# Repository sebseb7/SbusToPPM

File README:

This small Converter converts Futaba SBus Signal (inverted serial 100000 baud) to PPM (Pulse Position Modulation) or Spektrum Serial (serial 115200 baud)

I also sell them for 10 Euro (complete) or 1 Euro (pcb only)

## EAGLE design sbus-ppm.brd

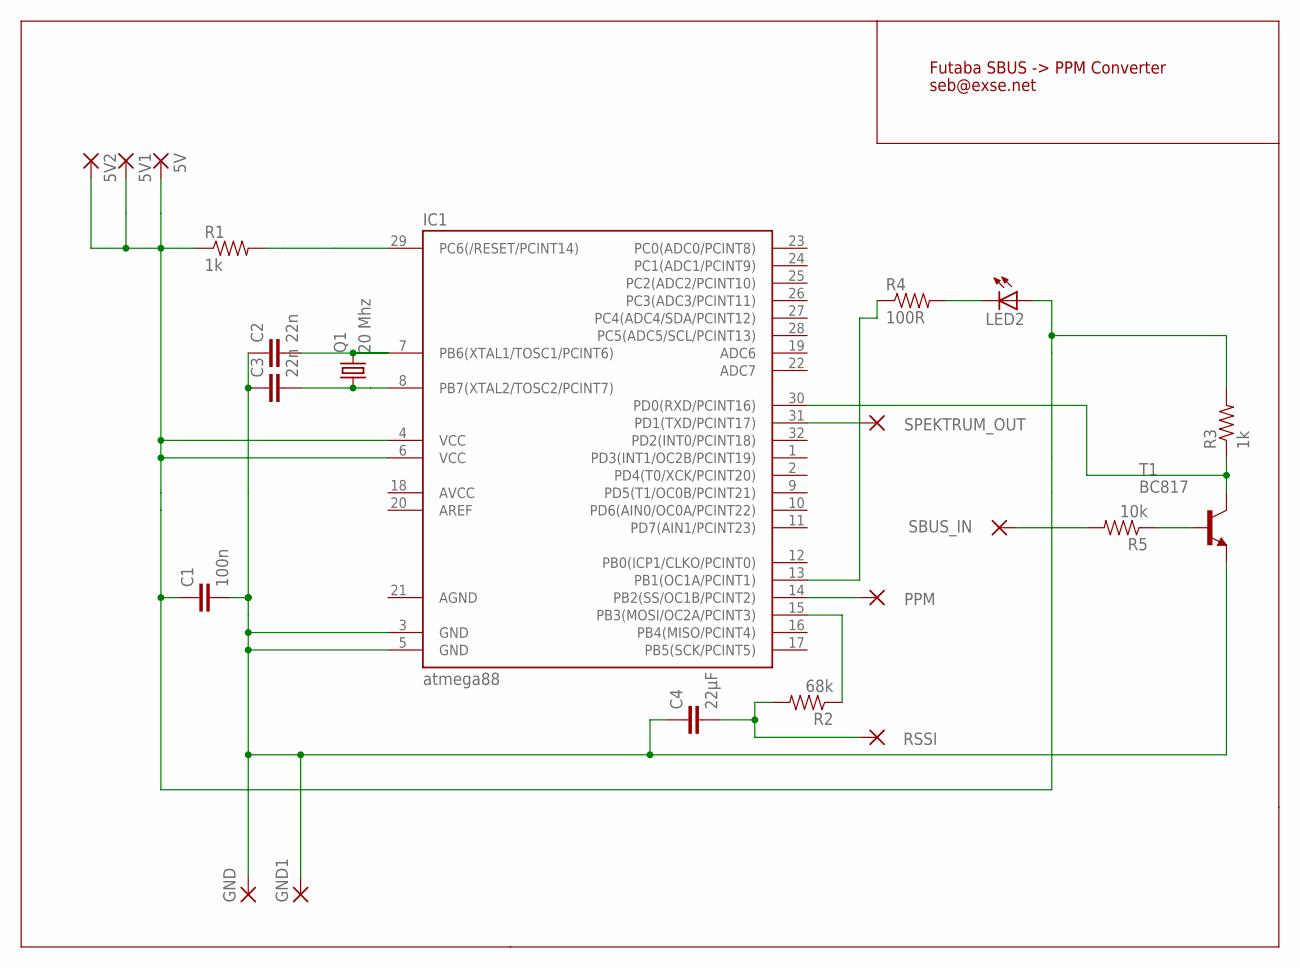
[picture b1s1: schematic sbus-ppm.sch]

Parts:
5V, 5V1, 5V2: SMD2; SMD1,27-2,54
C1: 100n; 0805
C2, C3: 22n; 0805
C4: 22µF; 0805
GND, GND1: SMD2; SMD1,27-2,54
IC1: atmega88; TQFP32-08
LED2: LEDCHIPLED_0805; CHIPLED_0805
PPM: SMD2; SMD1,27-2,54
Q1: 20 Mhz; X22
R1, R3: 1k; 0805
R2: 68k; 0805
R4: 100R; 0805
R5: 10k; 0805
RSSI: SMD2; SMD1,27-2,54
SBUS_IN: SMD2; SMD1,27-2,54
SPEKTRUM_OUT: SMD2; SMD1,27-2,54
T1: BC817; SOT23

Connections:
+5V: 5V.1, 5V1.1, 5V2.1, C1.1, IC1.4 (VCC), IC1.6 (VCC), LED2.A, R1.1, R3.2
AGND: IC1.21 (AGND)
GND: C1.2, C2.1, C3.1, C4.1, GND.1, GND1.1, IC1.3 (GND), IC1.5 (GND), T1.2 (E)
unnamed: IC1.15 (PB3(MOSI/OC2A/PCINT3)), R2.1
unnamed: IC1.14 (PB2(SS/OC1B/PCINT2)), PPM.1
unnamed: R5.2, SBUS_IN.1
unnamed: C4.2, R2.2, RSSI.1
unnamed: IC1.29 (PC6(/RESET/PCINT14)), R1.2
unnamed: C3.2, IC1.8 (PB7(XTAL2/TOSC2/PCINT7)), Q1.1
unnamed: C2.2, IC1.7 (PB6(XTAL1/TOSC1/PCINT6)), Q1.3 (2)
unnamed: R5.1, T1.1 (B)
unnamed: IC1.31 (PD1(TXD/PCINT17)), SPEKTRUM_OUT.1
unnamed: LED2.C, R4.2
unnamed: IC1.13 (PB1(OC1A/PCINT1)), R4.1
unnamed: IC1.30 (PD0(RXD/PCINT16)), R3.1, T1.3 (C)

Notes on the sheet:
Futaba SBUS -> PPM Converter
seb@exse.net

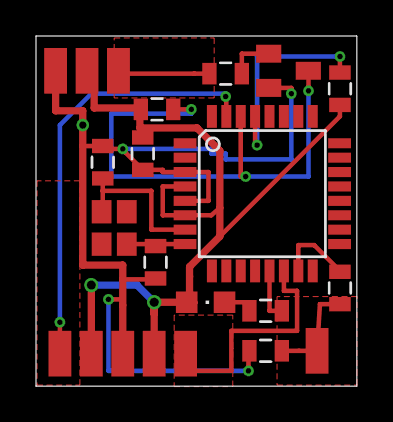
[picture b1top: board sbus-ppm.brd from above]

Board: 2 copper layers, 17.8 x 19.5 mm, 22 parts (0 on the bottom side), 14 nets.

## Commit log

2011-06-28 initial
2011-06-28 cleanup / gitignore
2011-06-28 cleanup
2011-07-01 removed check that could lead to problems
2011-07-01 added picture
2011-07-01 typo
2011-07-14 Edited README.mkd via GitHub
2012-02-27 whitespace cleanup
2012-02-27 new small Makefile
2012-07-11 readded as v6
2014-02-07 Update S-BUS -> PPM conversion
    Actual pulse widths and S-BUS values were read from a Futaba
    receiver, and a linear regression was used to determine a best fit for
    the measurements.
    The code and data used for the derivation can be found at
    https://gist.github.com/prattmic/8857047
    Basically, the S-BUS and raw PWM outputs were read from the Futaba
2014-02-07 Remove 'sei' in interrupt
    By definition, interrupts must be enabled to end up in an interrupt
    handler. Thus, enabling them is unnecessary.
2014-02-07 Perform floating point math outside of cleared interrupts
    The S-BUS to PPM conversion floating point math takes around 750us to
    complete. By doing the math when interrupts are enabled, service of the
    PPM timer interrupt is delayed, occassionally enough to cause two PPM
    packets to be sent back-to-back.
    Perform the math while interrupts are still enabled, then simply copy
    the results with interrupts disabled.
2016-05-01 pcb image
2016-05-01 font tweaks
2016-05-03 size
